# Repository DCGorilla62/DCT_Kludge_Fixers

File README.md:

# DCT_Kludge_Fixers
Fixing kludges on DCT Housekeeping box for pass throughs (heaters and temperatures) (North &amp; South)

## Specs
*Width: 2.5"
*Depth: 2.1"

Heater boards have trace width of 20 mils
Temp boards have trace width of 8 mils
## Status
*Heater North: Ready for review
*Heater South: Ready for review
*Temps North: Ready for review
*Temps South: Ready for review

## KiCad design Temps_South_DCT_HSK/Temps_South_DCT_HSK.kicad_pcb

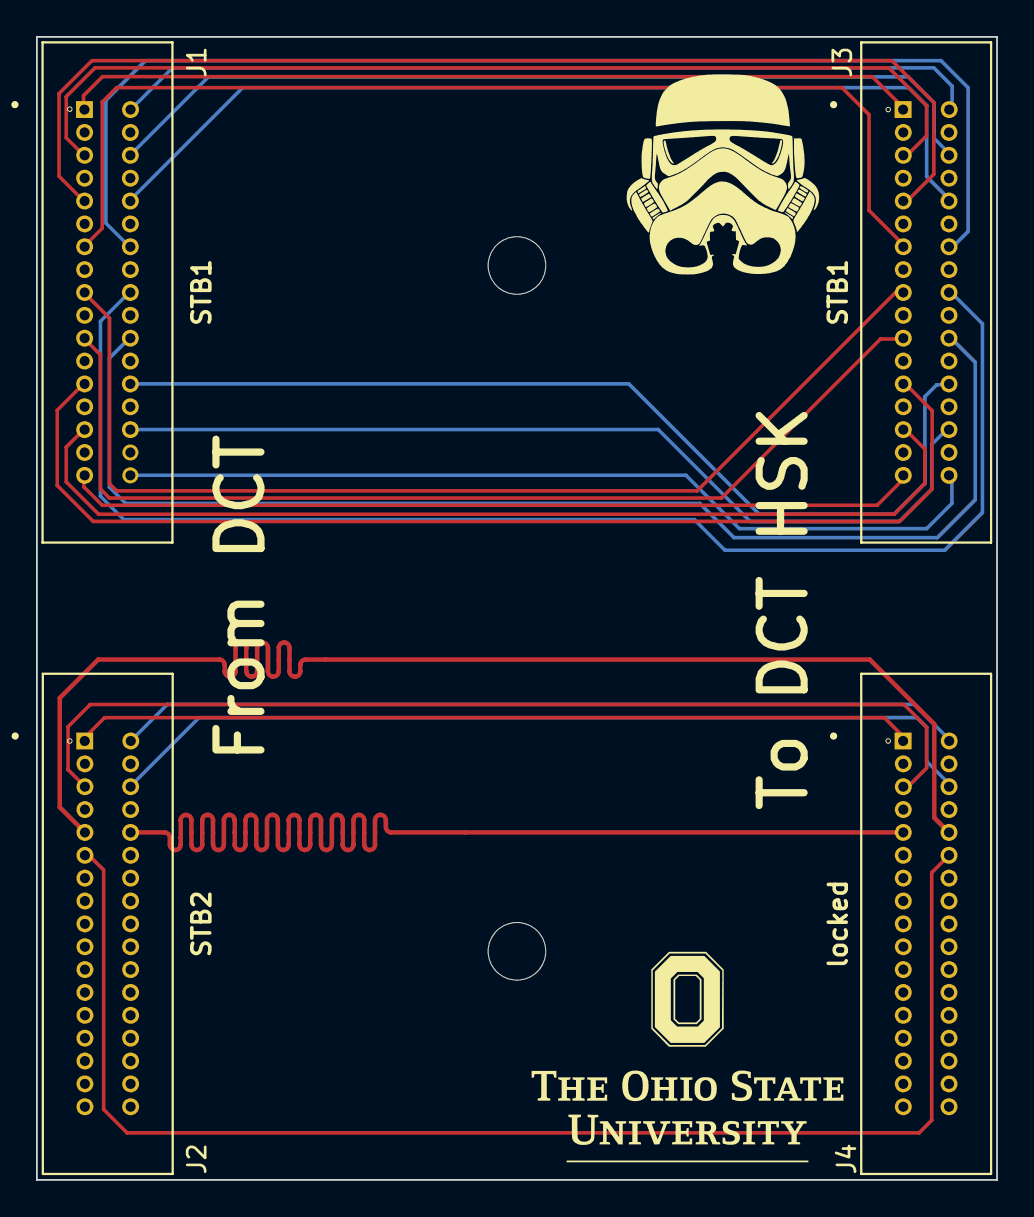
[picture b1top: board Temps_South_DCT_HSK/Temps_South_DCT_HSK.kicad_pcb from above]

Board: 2 copper layers, 53.3 x 63.5 mm, 4 parts (0 on the bottom side), 25 nets.

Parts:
J1: North_Temps_1; HELIX_DCT_ICDconnector34pin_corrected
J2: North_Temps_2; HELIX_DCT_ICDconnector34pin_corrected
J3: Internal_Temps_DCT_HSK_Box_1; HELIX_DCT_ICDconnector34pin_corrected
J4: Internal_Temps_DCT_HSK_Box_2; HELIX_DCT_ICDconnector34pin_corrected

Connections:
/TD1_1+: J1.1, J3.1
/TD1_1-: J1.2, J3.2
/TD1_5: J1.5, J3.5
/TD1_6: J1.6, J3.6
/TD1_9: J1.9, J3.9
/TD1_10: J1.10, J3.10
/TD1_13: J1.13, J3.13
/TD1_14: J1.14, J3.14
/TD1_17: J1.17, J3.17
/TD1_18: J1.18, J3.18
/TD1_21: J1.21, J3.21
/TD1_22: J1.22, J3.22
/TD1_25: J1.25, J3.25
/TD1_26: J1.26, J3.26
/TD1_29: J1.29, J3.29
/TD1_30: J1.30, J3.30
/TD1_33: J1.33, J3.33
/TD1_34: J1.34, J3.34
/TD2_1: J2.1, J4.1
/TD2_2: J2.2, J4.2
/TD2_5: J2.5, J4.5
/TD2_6: J2.6, J4.6
/TD2_9: J2.9, J4.10
/TD2_10: J2.10, J4.9
/TD2_11: J2.11, J4.12

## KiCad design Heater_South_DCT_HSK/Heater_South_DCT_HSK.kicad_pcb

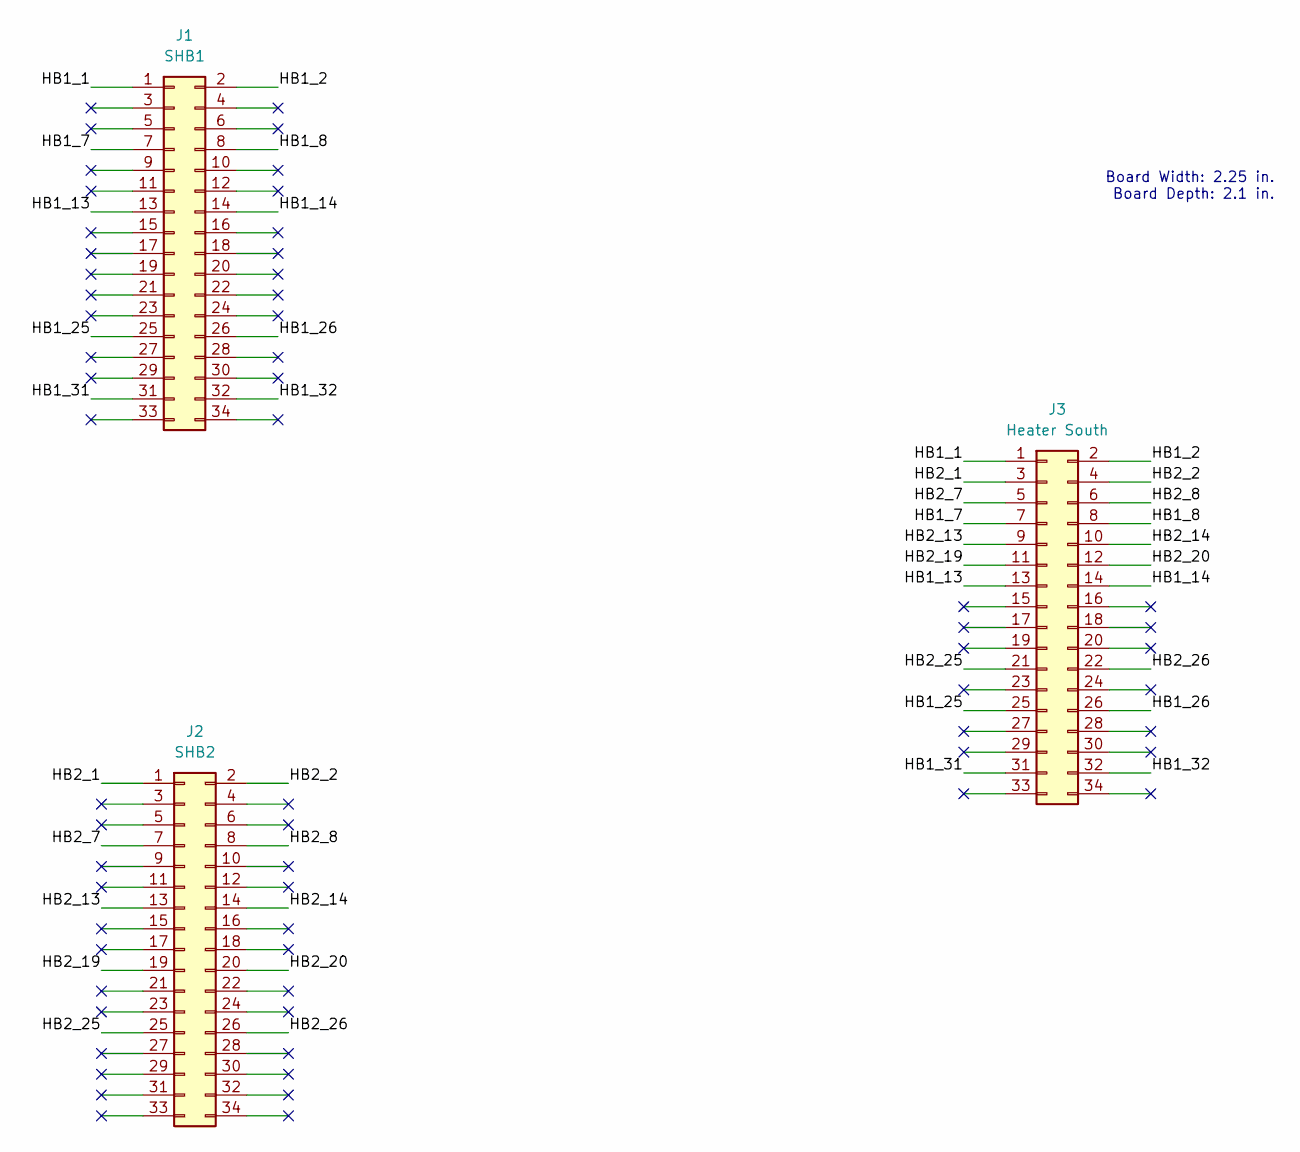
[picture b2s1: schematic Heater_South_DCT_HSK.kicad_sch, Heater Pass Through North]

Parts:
J1: SHB1; HELIX_DCT_ICDconnector34pin_corrected
J2: SHB2; HELIX_DCT_ICDconnector34pin_corrected
J3: Heater South; HELIX_DCT_ICDconnector34pin_corrected

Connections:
/HB1_1: J1.1, J3.1
/HB1_2: J1.2, J3.2
/HB1_7: J1.7, J3.7
/HB1_8: J1.8, J3.8
/HB1_13: J1.13, J3.13
/HB1_14: J1.14, J3.14
/HB1_25: J1.25, J3.25
/HB1_26: J1.26, J3.26
/HB1_31: J1.31, J3.31
/HB1_32: J1.32, J3.32
/HB2_1: J2.1, J3.3
/HB2_2: J2.2, J3.4
/HB2_7: J2.7, J3.5
/HB2_8: J2.8, J3.6
/HB2_13: J2.13, J3.9
/HB2_14: J2.14, J3.10
/HB2_19: J2.19, J3.11
/HB2_20: J2.20, J3.12
/HB2_25: J2.25, J3.21
/HB2_26: J2.26, J3.22

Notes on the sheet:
Board Width: 2.25 in. Board Depth: 2.1 in.

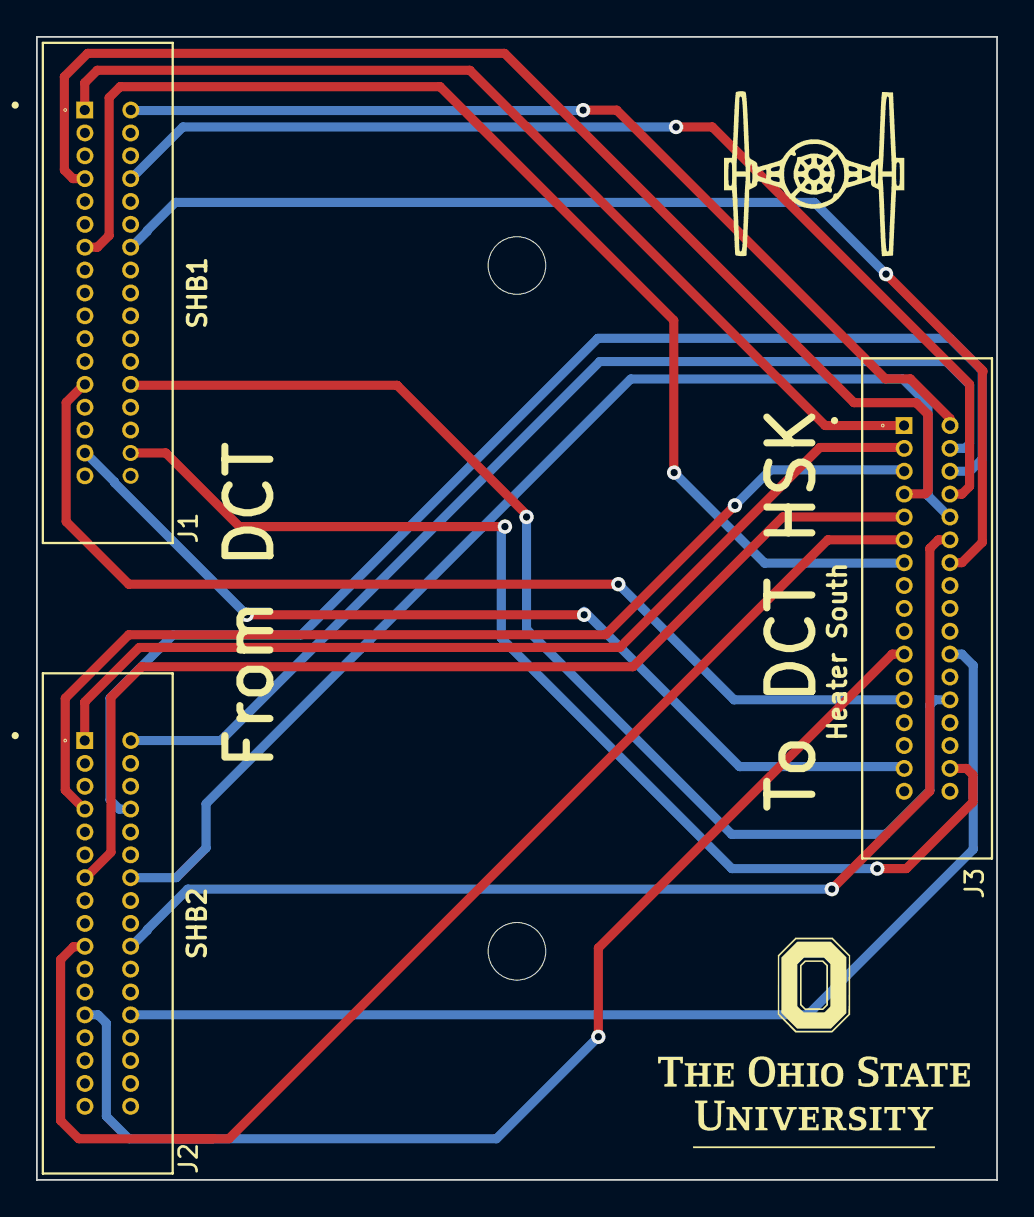
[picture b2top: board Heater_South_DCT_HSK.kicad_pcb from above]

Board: 2 copper layers, 53.3 x 63.5 mm, 3 parts (0 on the bottom side), 20 nets.

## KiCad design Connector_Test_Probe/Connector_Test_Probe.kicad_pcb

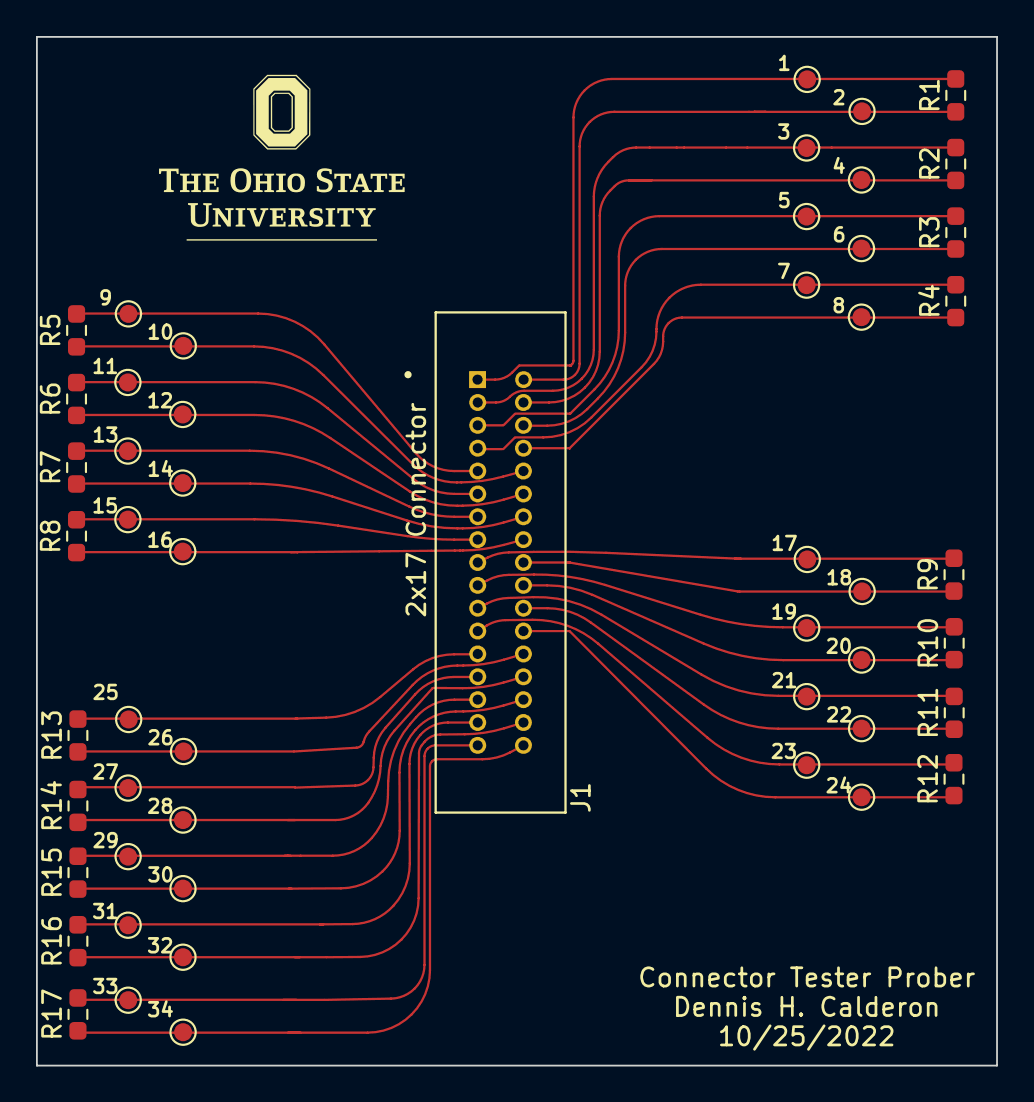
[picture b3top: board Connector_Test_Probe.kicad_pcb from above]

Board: 2 copper layers, 53.3 x 57.1 mm, 18 parts (0 on the bottom side), 34 nets.

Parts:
J1: 2x17 Connector; HELIX_DCT_ICDconnector34pin_corrected
R1, R2, R3, R4, R5, R6, R7, R8, R9, R10, R11, R12, R13, R14, R15, R16, R17: R_US; R_0603_1608Metric_Pad0.98x0.95mm_HandSolder

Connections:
unnamed: J1.1, R1.2
unnamed: J1.2, R1.1
unnamed: J1.3, R2.2
unnamed: J1.4, R2.1
unnamed: J1.5, R3.2
unnamed: J1.6, R3.1
unnamed: J1.7, R4.2
unnamed: J1.8, R4.1
unnamed: J1.9, R5.2
unnamed: J1.10, R5.1
unnamed: J1.11, R6.2
unnamed: J1.12, R6.1
unnamed: J1.13, R7.2
unnamed: J1.14, R7.1
unnamed: J1.15, R8.2
unnamed: J1.16, R8.1
unnamed: J1.17, R9.2
unnamed: J1.18, R9.1
unnamed: J1.19, R10.2
unnamed: J1.20, R10.1
unnamed: J1.21, R11.2
unnamed: J1.22, R11.1
unnamed: J1.23, R12.2
unnamed: J1.24, R12.1
unnamed: J1.25, R13.2
unnamed: J1.26, R13.1
unnamed: J1.27, R14.2
unnamed: J1.28, R14.1
unnamed: J1.29, R15.2
unnamed: J1.30, R15.1
unnamed: J1.31, R16.2
unnamed: J1.32, R16.1
unnamed: J1.33, R17.2
unnamed: J1.34, R17.1

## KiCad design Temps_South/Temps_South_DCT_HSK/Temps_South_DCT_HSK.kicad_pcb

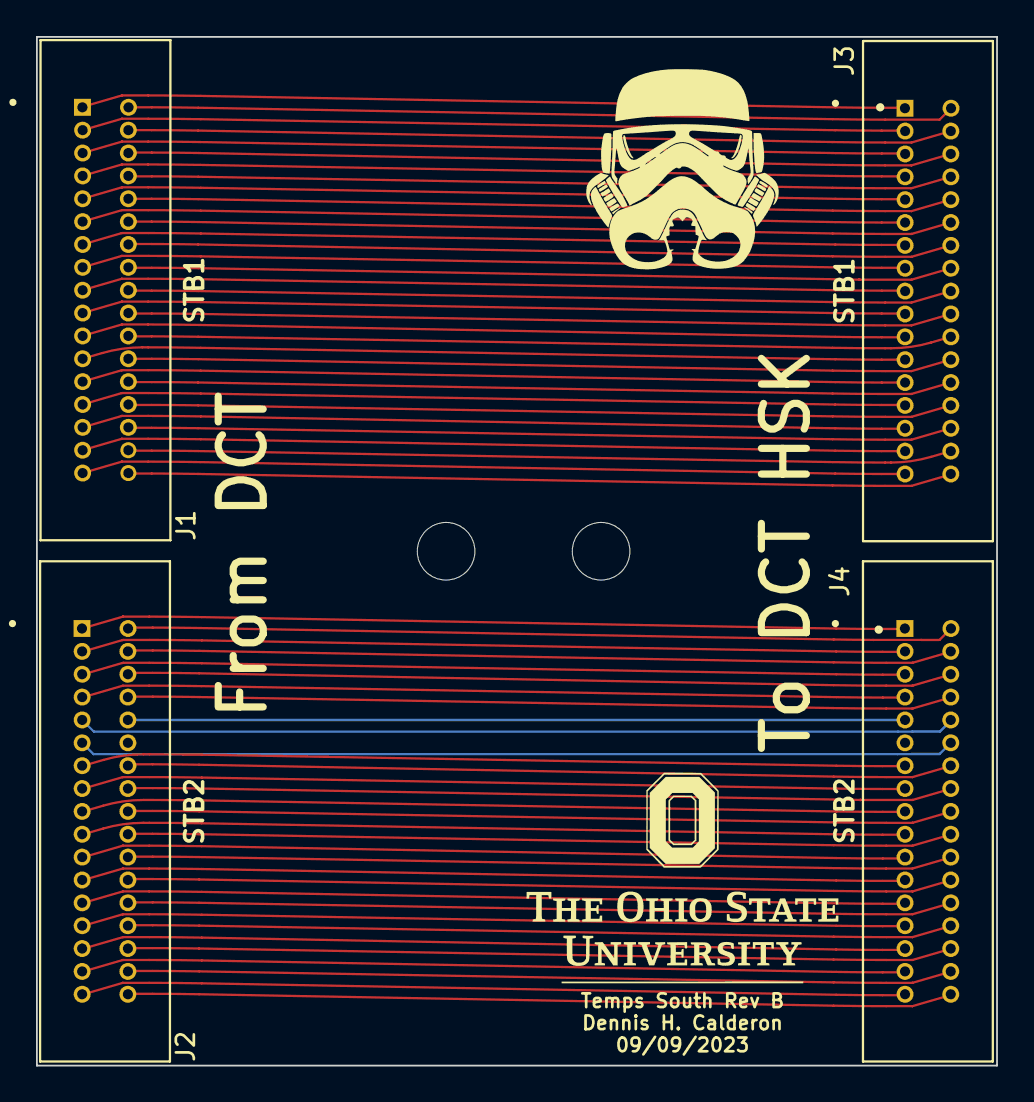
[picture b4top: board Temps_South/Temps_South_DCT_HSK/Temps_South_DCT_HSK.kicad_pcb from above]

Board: 2 copper layers, 53.3 x 57.1 mm, 5 parts (0 on the bottom side), 67 nets.

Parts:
J1: North_Temps_1; HELIX_DCT_ICDconnector34pin_corrected
J2: North_Temps_2; HELIX_DCT_ICDconnector34pin_corrected
J3: Internal_Temps_DCT_HSK_Box_1; HELIX_DCT_ICDconnector34pin_corrected
J4: Internal_Temps_DCT_HSK_Box_2; HELIX_DCT_ICDconnector34pin_corrected
REFe: MountingHole_3.2mm_M3

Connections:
/TD1_1: J1.1, J3.1
/TD1_2: J1.2, J3.2
/TD1_3: J1.3, J3.3
/TD1_4: J1.4, J3.4
/TD1_5: J1.5, J3.5
/TD1_6: J1.6, J3.6
/TD1_7: J1.7, J3.7
/TD1_8: J1.8, J3.8
/TD1_9: J1.9, J3.9
/TD1_10: J1.10, J3.10
/TD1_11: J1.11, J3.11
/TD1_12: J1.12, J3.12
/TD1_13: J1.13, J3.13
/TD1_14: J1.14, J3.14
/TD1_15: J1.15, J3.15
/TD1_16: J1.16, J3.16
/TD1_17: J1.17, J3.17
/TD1_18: J1.18, J3.18
/TD1_19: J1.19, J3.19
/TD1_20: J1.20, J3.20
/TD1_21: J1.21, J3.21
/TD1_22: J1.22, J3.22
/TD1_23: J1.23, J3.23
/TD1_24: J1.24, J3.24
/TD1_25: J1.25, J3.25
/TD1_26: J1.26, J3.26
/TD1_27: J1.27, J3.27
/TD1_28: J1.28, J3.28
/TD1_29: J1.29, J3.29
/TD1_30: J1.30, J3.30
/TD1_31: J1.31, J3.31
/TD1_32: J1.32, J3.32
/TD1_33: J1.33, J3.33
/TD1_34: J1.34, J3.34
/TD2_1: J2.1, J4.1
/TD2_2: J2.2, J4.2
/TD2_3: J2.3, J4.3
/TD2_4: J2.4, J4.4
/TD2_5: J2.5, J4.5
/TD2_6: J2.6, J4.6
/TD2_7: J2.7, J4.7
/TD2_8: J2.8, J4.8
/TD2_9: J2.9, J4.10
/TD2_10: J2.10, J4.9
/TD2_11: J2.11, J4.12
/TD2_13: J2.13, J4.13
/TD2_14: J2.14, J4.14
/TD2_15: J2.15, J4.15
/TD2_16: J2.16, J4.16
/TD2_17: J2.17, J4.17
/TD2_18: J2.18, J4.18
/TD2_19: J2.19, J4.19
/TD2_20: J2.20, J4.20
/TD2_21: J2.21, J4.21
/TD2_22: J2.22, J4.22
/TD2_23: J2.23, J4.23
/TD2_24: J2.24, J4.24
/TD2_25: J2.25, J4.25
/TD2_26: J2.26, J4.26
/TD2_27: J2.27, J4.27
/TD2_28: J2.28, J4.28
/TD2_29: J2.29, J4.29
/TD2_30: J2.30, J4.30
/TD2_31: J2.31, J4.31
/TD2_32: J2.32, J4.32
/TD2_33: J2.33, J4.33
/TD2_34: J2.34, J4.34

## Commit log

2022-10-20 Added Kicad files for South Heater pass through board for DCT.
2022-10-21 Added North and South boards. Ready for review.
2022-10-21 Fixed silkscreen on North board
2022-10-25 Made tester boad for 2x17 connector with probe spots
2022-10-25 Stupid
2022-10-25 Dumb
2022-10-25 .gitignore
2022-11-01 Added little 2 connectyor to 2 connector board.
2022-12-20 useless commit
2023-01-18 Updated .gitignore
2023-01-18 Corrected pinout for from NTB2 to DCT HSK
2023-01-23 Completed schematic & PCB for South Temp board.
2023-01-23 updated Temp boards
2023-01-26 Cleaned up directories
2023-09-08 Updated Temp North and Temp South Board, fixing shorted pins. Add M3 (#4-40) mounting holes as well.
2023-09-08 See previous commit
2023-09-10 Heater norths updated with large track width and mapping, as well as clear labels in schematic. Fits on same width PCB as original, depth is slightly increase and doesn't matter for front panel or bo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
2023-09-10 Improved temperature PCBs that dont rely on small traces and meet all design rules. Also includes tuned routing for RTD channel.
2023-09-12 Added mounting holes for North Temp. South Temp board updated based off K. McBride pull request.
2023-09-12 Updated Heater North and Heater South boards.
2023-09-12 Updated Heater South with correct mapping referencing DCT_Heater_Driver schematic. Updated silscreen on all boards. Generated fabrication files.
2023-09-12 Cleaned up Fab directories
2023-09-12 Updated .gitignore to exclude *.zip
2023-09-13 I was working towards fabrication. Chaged the KiCAD violation issues for each PCB to run all tests and make some important silkscreen font bigger. I also edited a few traces and even removed a few vi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
2023-09-14 Updated Heater and Temp PCBs to board size 2.5in x 2.1in. Updated traces and silkscreens
2023-09-14 Generated fab files for Heater and Temp Boards.
2023-09-14 Tuned RTD tracks for Temp boards
2023-09-14 Tuned RTD tracks on Temp boards
